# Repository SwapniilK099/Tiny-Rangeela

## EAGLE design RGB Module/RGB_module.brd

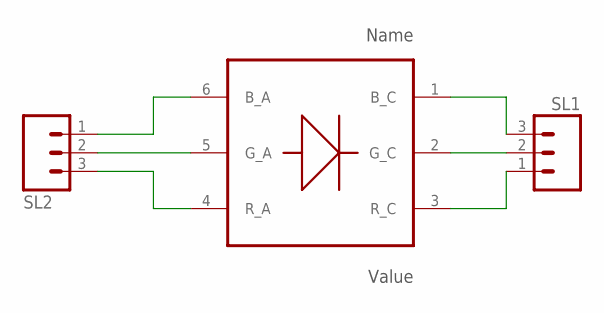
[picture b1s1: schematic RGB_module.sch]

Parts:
RGB_MODULE: RGB_SMD_3W; RGB_SMD_6PIN
SL1, SL2: M03; 03P

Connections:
B: RGB_MODULE.1 (B_C), SL1.3
C: RGB_MODULE.3 (R_C), SL1.1
G: RGB_MODULE.2 (G_C), SL1.2
unnamed: RGB_MODULE.4 (R_A), SL2.3
unnamed: RGB_MODULE.6 (B_A), SL2.1
unnamed: RGB_MODULE.5 (G_A), SL2.2

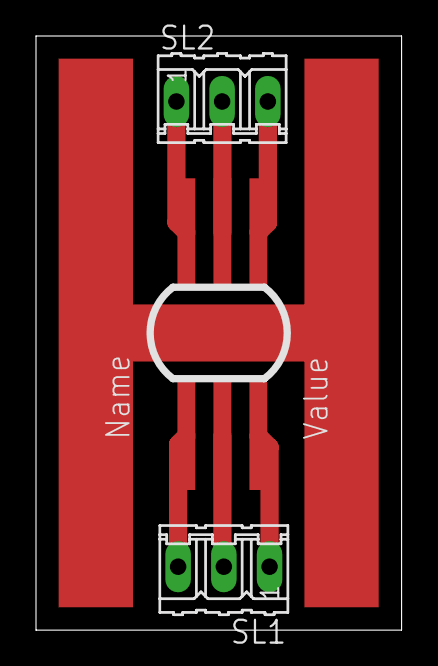
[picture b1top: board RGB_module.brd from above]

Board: 2 copper layers, 20.3 x 33.0 mm, 3 parts (0 on the bottom side), 6 nets.

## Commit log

2021-01-09 Add files via upload
    Eagle Files for RGB Module
2021-01-09 Arduino Code
    Arduino Code
2021-01-09 Description
    Visit: https://www.instructables.com/member/SwapniilK/
